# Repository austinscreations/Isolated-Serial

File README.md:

# Isolated-Serial
Allows for galvanic isolation of serial data

Initially created this as I've been working on the OXRS Black a rack controller for the [OXRS](https://oxrs.io) project.
I had made a mistake with the optoisolators so tried again with these mini breakouts and they work great.

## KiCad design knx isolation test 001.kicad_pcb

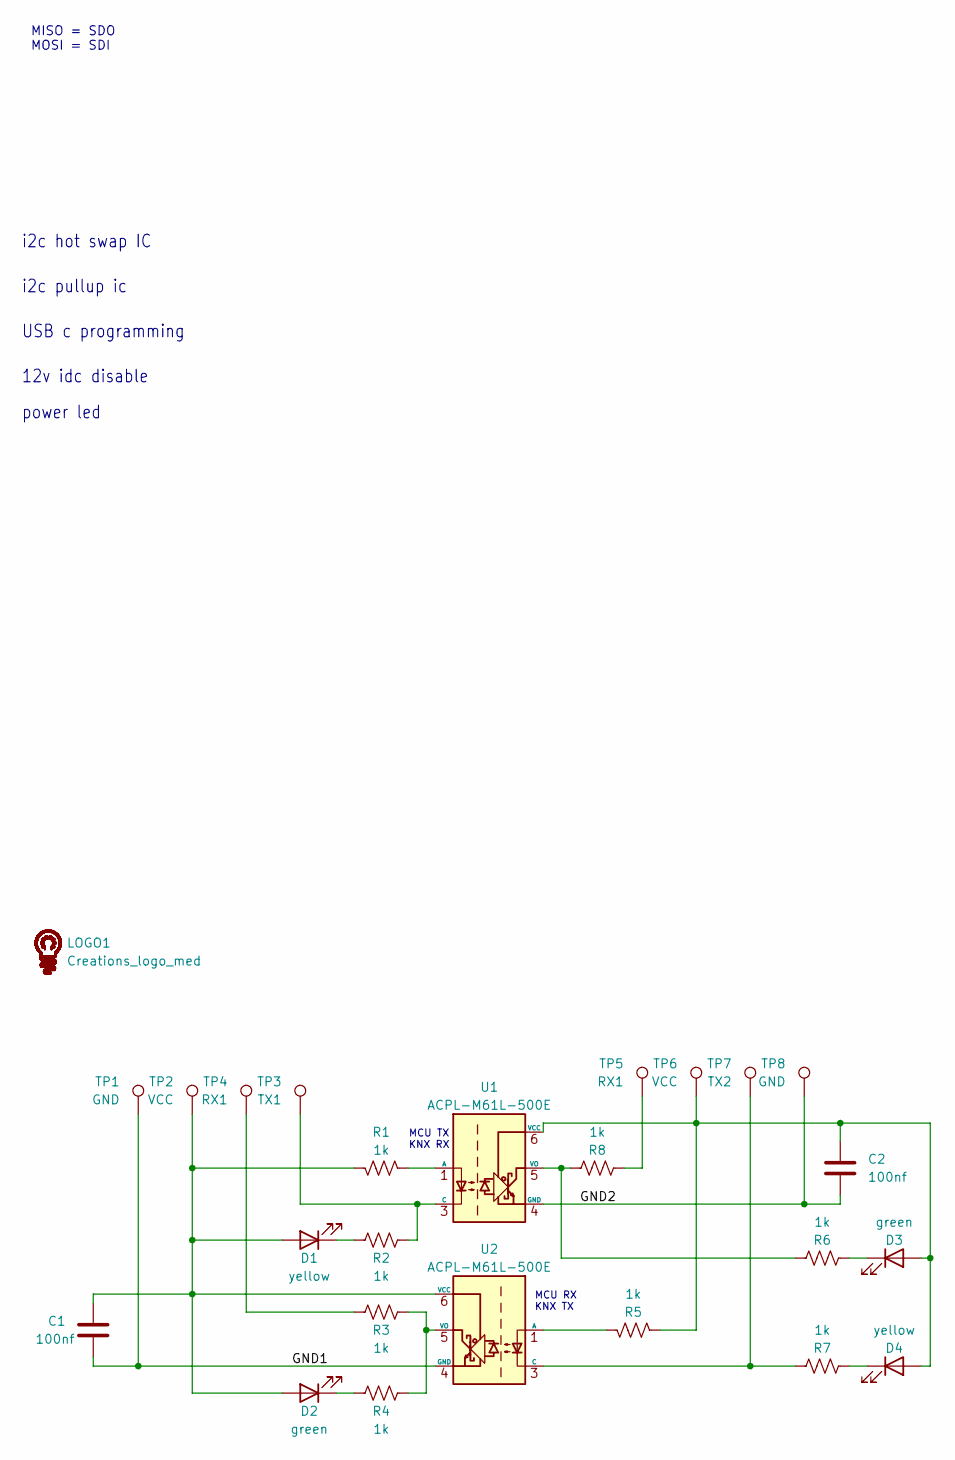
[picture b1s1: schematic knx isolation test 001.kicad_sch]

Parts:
C1, C2: 100nf; C_0603_1608Metric; LCSC C14663
D1, D4: yellow; LED_0603_1608Metric; LCSC C72038
D2, D3: green; LED_0603_1608Metric; LCSC C72043
LOGO1: Creations_logo_med; Creations logo med
R1, R2, R3, R4, R5, R6, R7, R8: 1k; R_0603_1608Metric; LCSC C21190
TP1, TP8: GND; TestPoint_Pad_D3.0mm
TP2, TP6: VCC; TestPoint_Pad_D3.0mm
TP3: TX1; TestPoint_Pad_D3.0mm
TP4, TP5: RX1; TestPoint_Pad_D3.0mm
TP7: TX2; TestPoint_Pad_D3.0mm
U1, U2: ACPL-M61L-500E; SO-5_4.4x3.6mm_P1.27mm; LCSC C44908

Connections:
/GND1: C1.2, TP1.1, U2.4 (GND)
/GND2: C2.2, TP8.1, U1.4 (GND)
unnamed: C1.1, D1.2 (A), D2.2 (A), R1.1, TP2.1, U2.6 (VCC)
unnamed: D1.1 (K), R2.1
unnamed: D2.1 (K), R4.1
unnamed: C2.1, D3.2 (A), D4.2 (A), R5.2, TP6.1, U1.6 (VCC)
unnamed: D3.1 (K), R6.1
unnamed: D4.1 (K), R7.1
unnamed: R3.1, TP4.1
unnamed: R8.1, TP5.1
unnamed: R1.2, U1.1 (A)
unnamed: R2.2, TP3.1, U1.3 (C)
unnamed: R6.2, R8.2, U1.5 (VO)
unnamed: R5.1, U2.1 (A)
unnamed: R7.2, TP7.1, U2.3 (C)
unnamed: R3.2, R4.2, U2.5 (VO)

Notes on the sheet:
power led
MISO = SDO MOSI = SDI
i2c hot swap IC
i2c pullup ic
MCU RX KNX TX
12v idc disable
USB c programming
MCU TX KNX RX

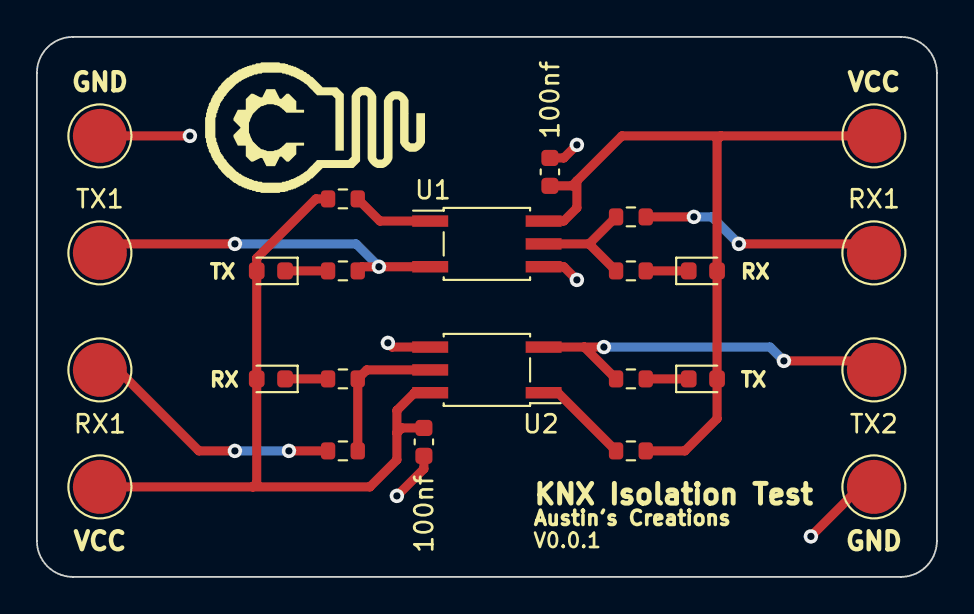
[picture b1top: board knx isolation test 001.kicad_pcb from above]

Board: 2 copper layers, 50.0 x 30.0 mm, 25 parts (0 on the bottom side), 16 nets.

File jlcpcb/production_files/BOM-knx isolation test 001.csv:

Comment,Designator,Footprint,LCSC
100nf,"C1,C2",C_0603_1608Metric,C14663
1k,"R1,R2,R3,R4,R5,R6,R7,R8",R_0603_1608Metric,C21190
ACPL-M61L-500E,"U1,U2",SO-5_4.4x3.6mm_P1.27mm,C44908
yellow,"D1,D4",LED_0603_1608Metric,C72038
green,"D2,D3",LED_0603_1608Metric,C72043

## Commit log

2024-03-29 add v001 files
2024-04-04 adding schematic in pdf
